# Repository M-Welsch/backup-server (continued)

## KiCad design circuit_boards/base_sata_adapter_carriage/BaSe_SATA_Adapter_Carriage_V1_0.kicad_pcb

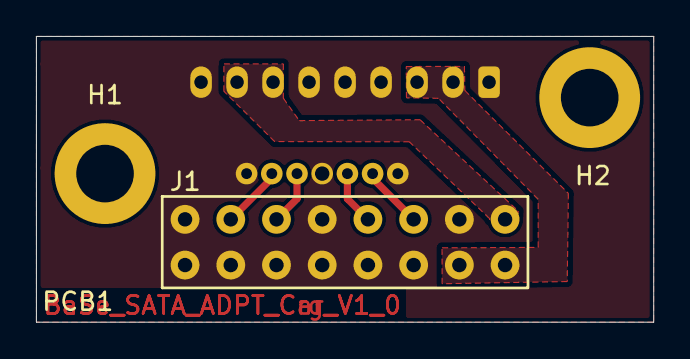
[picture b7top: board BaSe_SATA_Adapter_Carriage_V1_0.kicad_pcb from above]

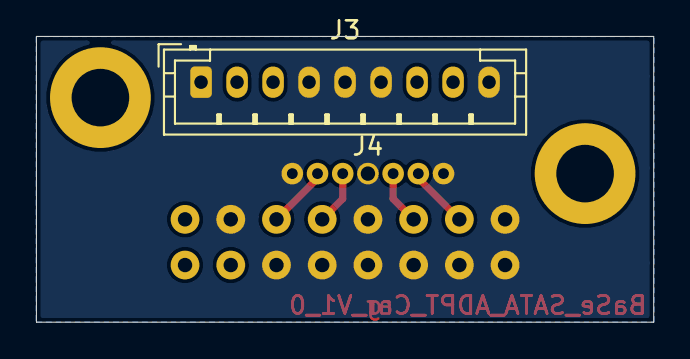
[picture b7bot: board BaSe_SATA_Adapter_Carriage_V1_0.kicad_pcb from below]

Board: 2 copper layers, 34.3 x 15.9 mm, 6 parts (2 on the bottom side), 7 nets.

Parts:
H1, H2: MountingHole_Pad; MountingHole_3.2mm_M3_DIN965_Pad
J1: Conn_02x08_Odd_Even; Conn_Spring_Counterpart_MaxMill_823-22-016-10-0001101
J3: Conn_01x09; JST_PH_B9B-PH-K_1x09_P2.00mm_Vertical
J4: Conn_01x07_Female; SATA_Cable_Intake
PCB1: BaSe_SATA_SpringConn_V1_0; BaSe_SATA_Adapter_Carriage_V1_0

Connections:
+5VA: J1.1, J3.7, J3.8
+12VA: J1.2, J1.4, J3.2, J3.3
/Cable_Rx+: J1.5, J4.6
/Cable_Rx-: J1.7, J4.5
/Cable_Tx+: J1.13, J4.2
/Cable_Tx-: J1.11, J4.3
GNDA: J1.3, J1.6, J1.8, J1.9, J1.10, J1.12, J1.14, J1.15, J1.16, J3.1, J3.4, J3.5, J3.6, J3.9, J4.1, J4.4, J4.7

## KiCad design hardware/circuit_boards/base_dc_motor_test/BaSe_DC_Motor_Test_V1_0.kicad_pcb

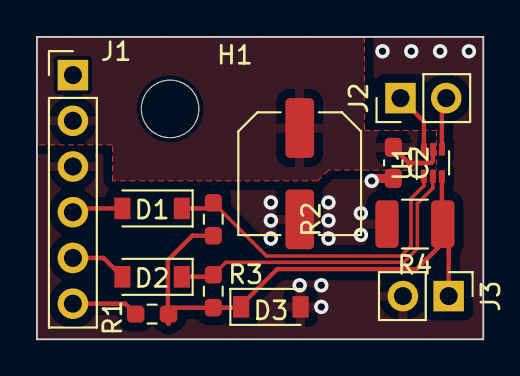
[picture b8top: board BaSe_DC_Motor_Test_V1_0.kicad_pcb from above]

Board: 2 copper layers, 24.8 x 16.8 mm, 14 parts (0 on the bottom side), 10 nets.

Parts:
C1: 220µF; C_Elec_6.3x7.7
C2: 100nF; C_0603_1608Metric_Pad1.08x0.95mm_HandSolder
D1, D2: D_Schottky; D_SOD-123
D3: 2.5V; D_SOD-123
H1: MountingHole; MountingHole_3.2mm_M3
J1: Conn_01x06; PinHeader_1x06_P2.54mm_Vertical
J2: MOTOR; PinHeader_1x02_P2.54mm_Vertical
J3: MEAS; PinHeader_1x02_P2.54mm_Vertical
R1: 1k; R_0603_1608Metric_Pad0.98x0.95mm_HandSolder
R2, R3: 10k; R_0603_1608Metric_Pad0.98x0.95mm_HandSolder
R4: R; R_1210_3225Metric_Pad1.30x2.65mm_HandSolder
U1: DRV8220; SOT-563

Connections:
/imotor: D3.1 (K), J3.1, R1.2, R2.2, R3.2, R4.1, U1.3 (GND)
/imotor_prot: J1.6, R1.1
/in1: D1.1 (K), R2.1, U1.1 (IN1)
/in1_mcu: D1.2 (A), J1.4
/in2: D2.1 (K), R3.1, U1.2 (IN2)
/in2_mcu: D2.2 (A), J1.5
GND: C1.2, C2.2, D3.2 (A), J1.1, J1.3, J3.2, R4.2
unnamed: J2.1, U1.6 (OUT1)
unnamed: J2.2, U1.4 (OUT2)
Vdrive: C1.1, C2.1, J1.2, U1.5 (VM)

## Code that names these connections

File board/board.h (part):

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#define GPIOA_ARD_A0                0U
#define GPIOA_ADC1_IN0              0U
#define GPIOA_ARD_A1                1U
#define STATOR_SUPPLY_SENSE         1U
#define GPIOA_ADC1_IN1              1U
#define GPIOA_ARD_D1                2U
#define GPIOA_USART2_TX             2U
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#define GPIOB_PIN14                 14U
#define GPIOB_PIN15                 15U

#define SW_HDD_ON                   0U
#define SW_HDD_OFF                  1U
#define SW_SBU_ON                   2U
#define SW_SBU_OFF                  3U
#define DISABLE_LM2596              4U
#define GPIOC_PIN5                  5U
#define GPIOC_PIN6                  6U
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#define LINE_nDOCKED2               PAL_LINE(GPIOB, 8U)
#define LINE_nDOCKED                PAL_LINE(GPIOB, 9U)
#define LINE_ARD_D6                 PAL_LINE(GPIOB, 10U)
#define LINE_SW_HDD_ON              PAL_LINE(GPIOC, SW_HDD_ON)
#define LINE_SW_HDD_OFF             PAL_LINE(GPIOC, SW_HDD_OFF)
#define LINE_SW_SBC_ON              PAL_LINE(GPIOC, SW_SBU_ON)
#define LINE_SW_SBC_OFF             PAL_LINE(GPIOC, SW_SBU_OFF)
#define LINE_DISABLE_LM2596         PAL_LINE(GPIOC, DISABLE_LM2596)
#define LINE_ARD_A5                 PAL_LINE(GPIOC, 0U)
#define LINE_ADC1_IN11              PAL_LINE(GPIOC, 0U)
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/*
 * GPIOA setup:
 *
 * PA0  - ARD_A0 ADC1_IN0           (input pullup).
 * PA1  - ARD_A1 ADC1_IN1           (input pullup).
 * PA2  - ARD_D1 USART2_TX          (alternate 1).
 * PA3  - ARD_D0 USART2_RX          (alternate 1).
 * PA4  - ARD_A2 ADC1_IN4           (input pullup).
 * PA5  - LED_GREEN                 (output pushpull high).
 * PA6  - ARD_D12                   (input pullup).
 * PA7  - ARD_D11                   (input pullup).
 * PA8  - ARD_D7                    (input pullup).
 * PA9  - ARD_D8                    (input pullup).
 * PA10 - ARD_D2                    (input pullup).
 * PA11 - PIN11                     (input pullup).
 * PA12 - PIN12                     (input pullup).
 * PA13 - SWDIO                     (alternate 0).
 * PA14 - SWCLK                     (alternate 0).
 * PA15 - PIN15                     (input pullup).
 */
#define VAL_GPIOA_MODER             (PIN_MODE_INPUT(GPIOA_ARD_A0) |         \
                                     PIN_MODE_INPUT(STATOR_SUPPLY_SENSE) |         \
                                     PIN_MODE_ALTERNATE(GPIOA_ARD_D1) |     \
                                     PIN_MODE_ALTERNATE(GPIOA_ARD_D0) |     \
                                     PIN_MODE_INPUT(GPIOA_ARD_A2) |         \
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                                     PIN_MODE_ALTERNATE(GPIOA_SWCLK) |      \
                                     PIN_MODE_INPUT(GPIOA_PIN15))
#define VAL_GPIOA_OTYPER            (PIN_OTYPE_PUSHPULL(GPIOA_ARD_A0) |     \
                                     PIN_OTYPE_PUSHPULL(STATOR_SUPPLY_SENSE) |     \
                                     PIN_OTYPE_PUSHPULL(GPIOA_ARD_D1) |     \
                                     PIN_OTYPE_PUSHPULL(GPIOA_ARD_D0) |     \
                                     PIN_OTYPE_PUSHPULL(GPIOA_ARD_A2) |     \
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/*
 * GPIOB setup:
 *
 * PB0  - ARD_A3 ADC1_IN8           (input pullup).
 * PB1  - PIN1                      (input pullup).
 * PB2  - PIN2                      (input pullup).
 * PB3  - SWO ARD_D3                (alternate 0).
 * PB4  - ARD_D5                    (input pullup).
 * PB5  - ARD_D4                    (input pullup).
 * PB6  - ARD_D10                   (input pullup).
 * PB7  - PIN7                      (input pullup).
 * PB8  - ARD_D15                   (input pullup).
 * PB9  - ARD_D14                   (input pullup).
 * PB10 - ARD_D6                    (input pullup).
 * PB11 - PIN11                     (input pullup).
 * PB12 - PIN12                     (input pullup).
 * PB13 - PIN13                     (input pullup).
 * PB14 - PIN14                     (input pullup).
 * PB15 - PIN15                     (input pullup).
 */
#define VAL_GPIOB_MODER             (PIN_MODE_INPUT(GPIOB_ARD_A3) |         \
                                     PIN_MODE_INPUT(GPIOB_PIN1) |           \
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/*
 * GPIOC setup:
 *
 * PC0  - ARD_A5 ADC1_IN11          (input pullup).
 * PC1  - ARD_A4 ADC1_IN10          (input pullup).
 * PC2  - PIN2                      (input pullup).
 * PC3  - PIN3                      (input pullup).
 * PC4  - PIN4                      (input pullup).
 * PC5  - PIN5                      (input pullup).
 * PC6  - PIN6                      (input pullup).
 * PC7  - ARD_D9                    (input pullup).
 * PC8  - PIN8                      (input pullup).
 * PC9  - PIN9                      (input pullup).
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 * PC14 - OSC32_IN                  (input floating).
 * PC15 - OSC32_OUT                 (input floating).
 */
#define VAL_GPIOC_MODER             (PIN_MODE_OUTPUT(SW_HDD_ON) |         \
                                     PIN_MODE_OUTPUT(SW_HDD_OFF) |         \
                                     PIN_MODE_OUTPUT(SW_SBU_ON) |           \
                                     PIN_MODE_OUTPUT(SW_SBU_OFF) |           \
                                     PIN_MODE_OUTPUT(DISABLE_LM2596) |           \
                                     PIN_MODE_INPUT(GPIOC_PIN5) |           \
                                     PIN_MODE_INPUT(GPIOC_PIN6) |           \
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                                     PIN_MODE_INPUT(GPIOC_BUTTON) |         \
                                     PIN_MODE_INPUT(GPIOC_OSC32_IN) |       \
                                     PIN_MODE_INPUT(GPIOC_OSC32_OUT))
#define VAL_GPIOC_OTYPER            (PIN_OTYPE_PUSHPULL(SW_HDD_ON) |     \
                                     PIN_OTYPE_PUSHPULL(SW_HDD_OFF) |     \
                                     PIN_OTYPE_PUSHPULL(SW_SBU_ON) |       \
                                     PIN_OTYPE_PUSHPULL(SW_SBU_OFF) |       \
                                     PIN_OTYPE_PUSHPULL(DISABLE_LM2596) |       \
                                     PIN_OTYPE_PUSHPULL(GPIOC_PIN5) |       \
                                     PIN_OTYPE_PUSHPULL(GPIOC_PIN6) |       \
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                                     PIN_OTYPE_PUSHPULL(GPIOC_BUTTON) |     \
                                     PIN_OTYPE_PUSHPULL(GPIOC_OSC32_IN) |   \
                                     PIN_OTYPE_PUSHPULL(GPIOC_OSC32_OUT))
#define VAL_GPIOC_OSPEEDR           (PIN_OSPEED_HIGH(SW_HDD_ON) |        \
                                     PIN_OSPEED_HIGH(SW_HDD_OFF) |        \
                                     PIN_OSPEED_HIGH(SW_SBU_ON) |          \
                                     PIN_OSPEED_HIGH(SW_SBU_OFF) |          \
                                     PIN_OSPEED_HIGH(DISABLE_LM2596) |          \
                                     PIN_OSPEED_HIGH(GPIOC_PIN5) |          \
                                     PIN_OSPEED_HIGH(GPIOC_PIN6) |          \
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                                     PIN_OSPEED_HIGH(GPIOC_BUTTON) |        \
                                     PIN_OSPEED_HIGH(GPIOC_OSC32_IN) |      \
                                     PIN_OSPEED_HIGH(GPIOC_OSC32_OUT))
#define VAL_GPIOC_PUPDR             (PIN_PUPDR_FLOATING(SW_HDD_ON) |       \
                                     PIN_PUPDR_FLOATING(SW_HDD_OFF) |       \
                                     PIN_PUPDR_FLOATING(SW_SBU_ON) |         \
                                     PIN_PUPDR_FLOATING(SW_SBU_OFF) |         \
                                     PIN_PUPDR_FLOATING(DISABLE_LM2596) |         \
                                     PIN_PUPDR_PULLUP(GPIOC_PIN5) |         \
                                     PIN_PUPDR_PULLUP(GPIOC_PIN6) |         \
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                                     PIN_PUPDR_FLOATING(GPIOC_BUTTON) |     \
                                     PIN_PUPDR_FLOATING(GPIOC_OSC32_IN) |   \
                                     PIN_PUPDR_FLOATING(GPIOC_OSC32_OUT))
#define VAL_GPIOC_ODR               (PIN_ODR_LOW(SW_HDD_ON) |           \
                                     PIN_ODR_LOW(SW_HDD_OFF) |           \
                                     PIN_ODR_LOW(SW_SBU_ON) |             \
                                     PIN_ODR_LOW(SW_SBU_OFF) |             \
                                     PIN_ODR_HIGH(DISABLE_LM2596) |             \
                                     PIN_ODR_HIGH(GPIOC_PIN5) |             \
                                     PIN_ODR_HIGH(GPIOC_PIN6) |             \
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                                     PIN_ODR_HIGH(GPIOC_BUTTON) |           \
                                     PIN_ODR_HIGH(GPIOC_OSC32_IN) |         \
                                     PIN_ODR_HIGH(GPIOC_OSC32_OUT))
#define VAL_GPIOC_AFRL              (PIN_AFIO_AF(SW_HDD_ON, 0U) |        \
                                     PIN_AFIO_AF(SW_HDD_OFF, 0U) |        \
                                     PIN_AFIO_AF(SW_SBU_ON, 0U) |          \
                                     PIN_AFIO_AF(SW_SBU_OFF, 0U) |          \
                                     PIN_AFIO_AF(DISABLE_LM2596, 0U) |          \
                                     PIN_AFIO_AF(GPIOC_PIN5, 0U) |          \
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
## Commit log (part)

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2022-03-30 including sbu, bcu and webapp
2022-03-30 restructure
2022-03-30 add power pcb
2022-03-31 add hmi circuit board
2022-03-31 add sata adapter pcbs
2022-04-08 add 3d printing parts
2022-04-08 add rev3a BOM
2022-04-08 add rev3b BOM
2022-04-08 add 3d printing parts explosion drawings
2024-01-04 [Orga] including sbu, bcu and webapp
2024-01-04 [Orga]restructure
2024-01-04 [HW] add power pcb
2024-01-04 [HW] add hmi circuit board
2024-01-04 [HW] add sata adapter pcbs
2024-01-04 [HW] add 3d printing parts
2024-01-04 [HW] add rev3a BOM
2024-01-04 [HW] add rev3b BOM
2024-01-04 [HW] add 3d printing parts explosion drawings
2024-01-04 [Orga] cleanup
2024-01-04 [PCU] create board-files
2024-01-04 [HW] v3 with raspberry pi 4
2024-01-04 [HW] production ready version of base pwr
2024-01-04 [PCU] restructure command parsing
2024-01-04 [HW] first version of sata adapter boards
2024-01-04 [PCU] introduce alarmClock
2024-01-04 [HW] new base pwr version
2024-01-04 [HW] production ready versions of sata adapter boards
2024-01-04 [PCU] setting backup and wakeup time
2024-01-04 [HW] first hmi board version
2024-01-04 [PCU] implement docking
2024-01-04 [HW] production ready version of base hmi
2024-01-04 [PCU] add alarmclock things
2024-01-04 [PCU] implement wakeup reason
2024-01-04 [PCU] implement bcu communication with shell
2024-01-04 [PCU] implement 5v control
2024-01-04 [HW] second version, never built up. First version has no kicad files, just hand-sketches
2024-01-04 [HW] add 3d printing parts (stl files)
2024-01-04 [PCU] implementing statemachine with chibiOS event system
2024-01-04 [PCU] introduce simple endswitch request
2024-01-04 [PCU] introduce measurement for adc
2024-01-04 [PCU] relay control implemented
2024-01-04 [PCU] introduce pushbuttons
2024-01-04 [PCU] implement and test display
2024-01-04 [HW] Initial commit
2024-01-04 [HW] v2.0, made of the blue breadboard
2024-01-04 [HW] add bill of materials
2024-01-04 [HW] add hardware
2024-01-04 [HW] test pcb for the dockable usb connection
2024-01-04 [HW] testboard for the motor driver and current measurement
2024-01-04 [HW] BaSe_PWR_V4_0: create PCBs
2024-01-04 first draft
2024-01-04 add logs
2024-01-04 add log messages
2024-01-04 engage, disengage, backup works
2024-01-07 [PCU] activate debug usart
2024-01-07 Update issue templates
2024-01-07 [BCU] add relevant linux config files. Add waiting time to bcu program
2024-01-08 possible fix for #19 and implement shutdown properly
2024-01-09 [BCU] add handshake with pcu as described in #20
2024-01-09 [PCU] introduce getter for current state, implement custom shutdown delay
2024-01-09 [PCU] increase maximum shell arguments to 10
2024-01-11 [PCU] introduce debug module and put messages
2024-01-11 [PCU] implement version getter
2024-01-11 [BCU] refactor logmessages
2024-01-11 Apply suggestions from code review
2024-01-11 Bcu/init (#24)
    * [BCU] Milestone MVP
2024-01-11 [HIL] first sketch
2024-01-14 [HIL] another sketch
2024-01-14 Pcu/debug usart (#23)
    [PCU] debug usart
2024-01-15 [BCU] interface with HIL
2024-01-15 [HIL] execution works. Assertions upcoming
2024-01-15 [HIL] automated start and stop bcu works. Assertions still upcoming
2024-01-15 [BCU] adjust setup script
2024-01-15 [HIL] stop bcu in normal mode as well. Assertions still upcoming
2024-01-16 [HIL] introduce hil-specific logfile
2024-01-16 [HIL] add real start/stop scripts
2024-01-16 [BCU] add nonfunctional graceful shutdown handling
2024-01-18 fix bug #28
2024-01-18 Refactoring
2024-01-18 Remove test args
2024-01-19 [HIL] scripts for starting bcu service in normal mode
2024-01-19 Refactoring, restructuring
2024-01-19 HIL first sketch (#29)
    [HIL] runs bcu with test-config and gathers logfiles
2024-01-19 Bcu mvp (#32)
    * [BaSe] MVP
2024-01-21 [BCU] add udev rule for real backup hdd, set time to wake up to 12h
2024-01-22 Update issue templates
    add bug template
2024-01-25 [BCU] testing for #34 (PCU node not there)
2024-01-26 [BCU] minor refactoring
2024-01-26 [BCU] add udev rule for real backup hdd, set time to wake up to 12h (#36)
    [BCU] minor changes before longterm test
2024-01-27 [BCU] fixed backup target path
2024-01-28 [HW] add hw rev4 3d printing parts
2024-02-04 fix backup target path (again)
2024-02-04 [PCU] initial dock state is determined by digital input
2024-02-04 [PCU] initial dock state is determined by digital input (#42)
2025-06-14 [BCU] fix issue 47
2025-06-14 [BCU] attemt to fix issue 47. Testing on HW rev4
2025-12-28 Fix/issue47 permissions and ownership (#48)
2025-12-28 [BCU] attemt to fix issue 49. Testing on HW rev4
